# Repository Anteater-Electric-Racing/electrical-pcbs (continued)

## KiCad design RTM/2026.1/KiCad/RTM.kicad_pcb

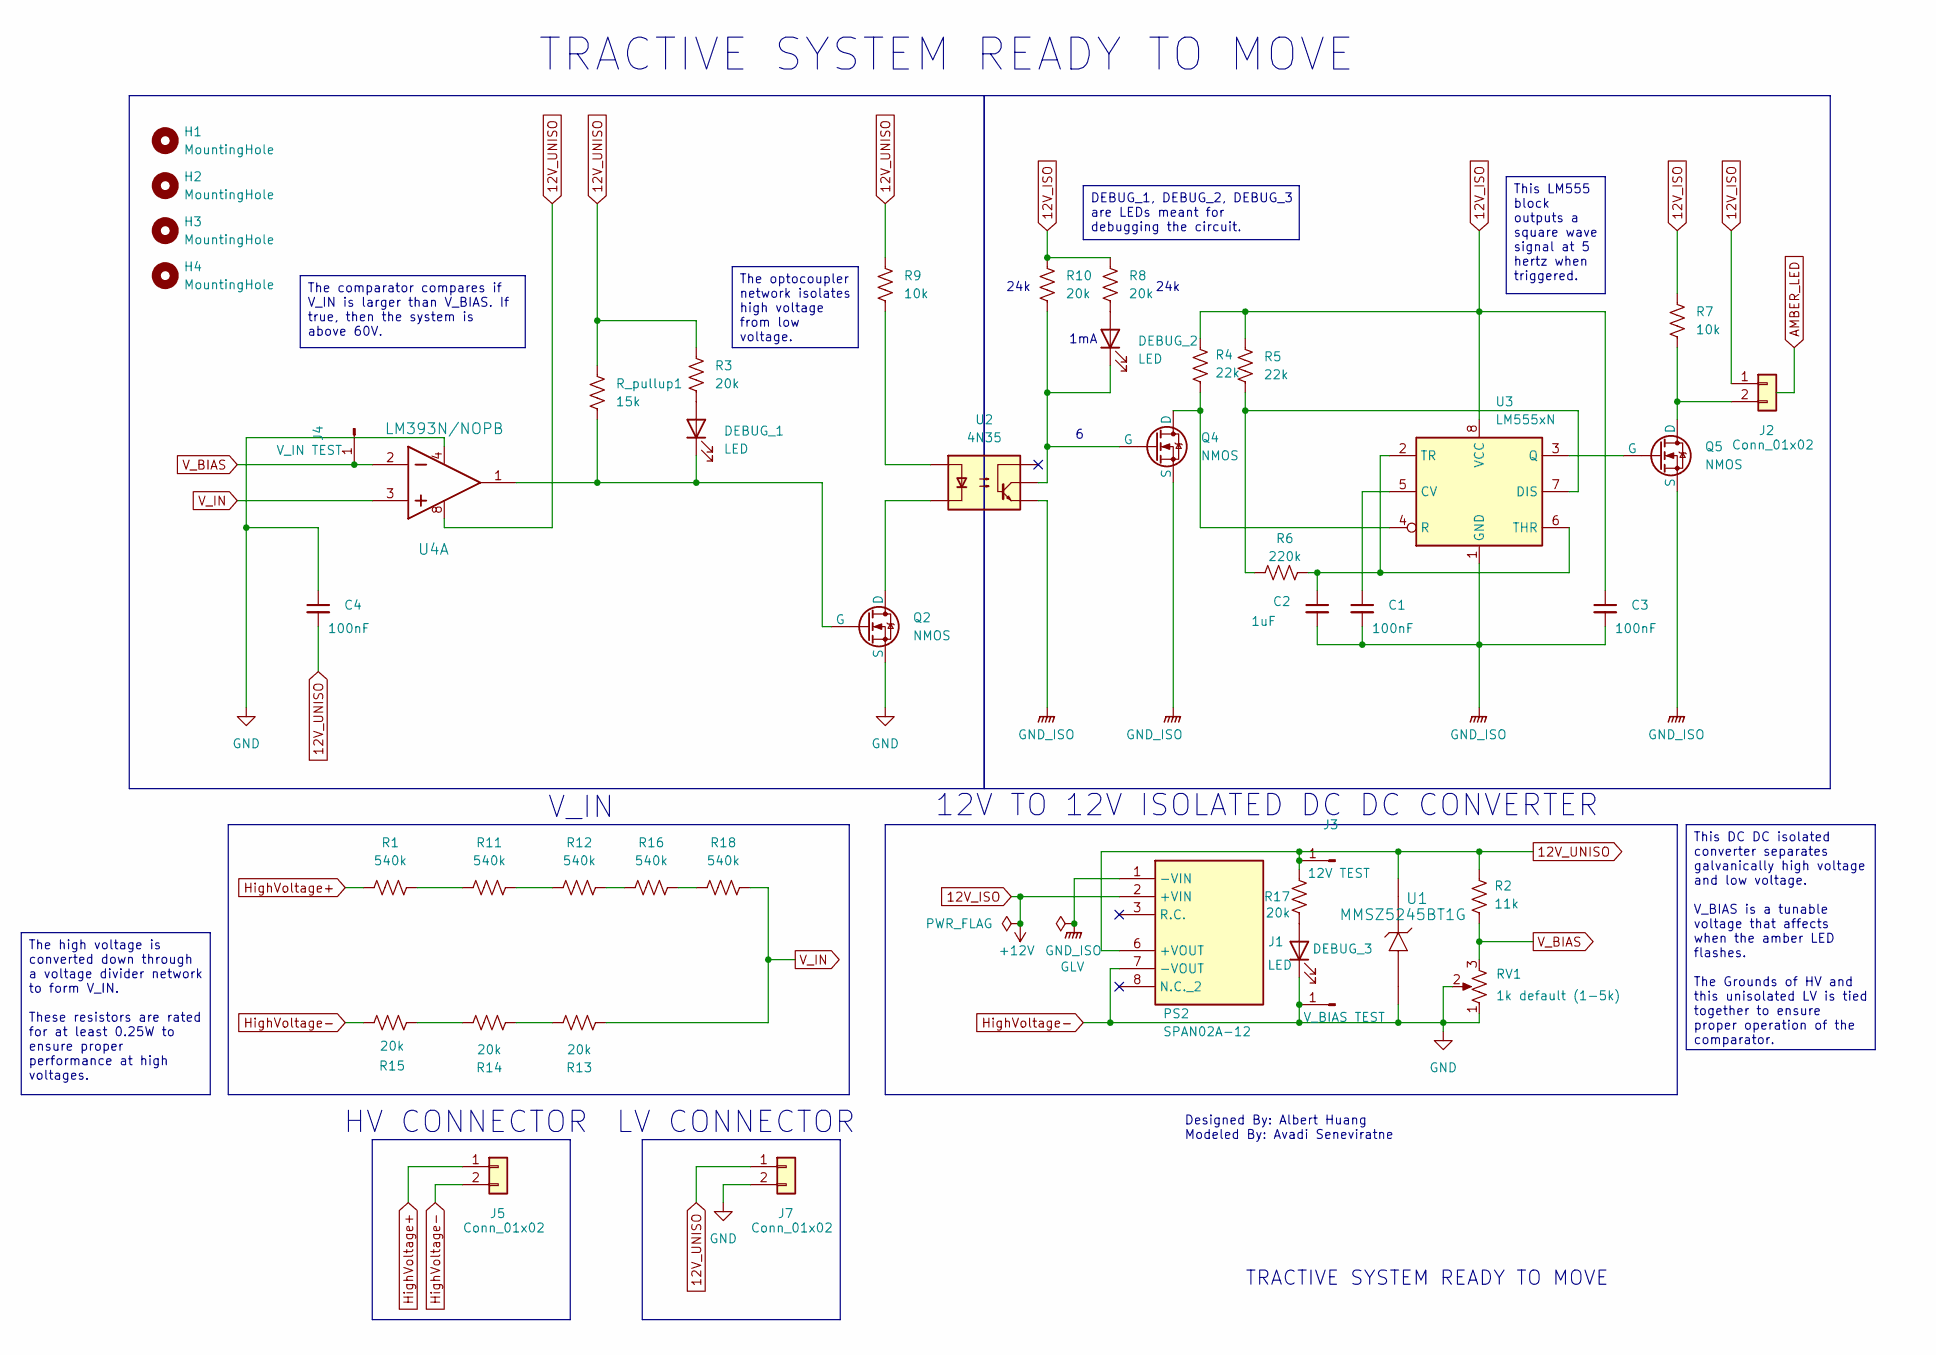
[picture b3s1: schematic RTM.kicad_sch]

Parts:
C1, C3, C4: 100nF; C_0805_2012Metric
C2: 1uF; C_0805_2012Metric
DEBUG_1, DEBUG_2, DEBUG_3: LED; LED_D5.0mm
H1, H2, H3, H4: MountingHole; MountingHole_3.2mm_M3
J1: V_BIAS TEST; TestPoint_Loop_D3.80mm_Drill2.0mm
J2, J5, J7: Conn_01x02; Molex_Mini-Fit_Jr_5566-02A2_2x01_P4.20mm_Vertical
J3: 12V TEST; TestPoint_Loop_D3.80mm_Drill2.0mm
J4: V_IN TEST; TestPoint_Loop_D3.80mm_Drill2.0mm
PS2: SPAN02A-12; SPAN02A12; Mouser Part Number 709-SPAN02A-12
Q2, Q4, Q5: NMOS; TO-220-3_Vertical
R1, R11, R12, R16, R18: 540k; R_0805_2012Metric
R2: 11k; R_0805_2012Metric
R3, R8, R10, R13, R14, R15, R17: 20k; R_0805_2012Metric
R4, R5: 22k; R_0805_2012Metric
R6: 220k; R_0805_2012Metric
R7, R9: 10k; R_0805_2012Metric
RV1: 1k default (1-5k); Potentiometer_Bourns_3296Y_Vertical
R_pullup1: 15k; R_0805_2012Metric
U1: MMSZ5245BT1G; D_SOD-123
U2: 4N35; DIP-6_W7.62mm
U3: LM555xN; DIP-8_W7.62mm
U4: LM393N/NOPB; DIP-8_W7.62mm

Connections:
12V_ISO: C3.1, J2.1, PS2.2 (+VIN), R4.1, R5.1, R7.1, R8.1, R10.1, U3.8 (VCC)
12V_UNISO: C4.2, J3.1, J7.1, PS2.6 (+VOUT), R2.1, R3.1, R9.1, R17.1, R_pullup1.1, U1.1 (CATHODE), U4.8 (V+)
GND_ISO: C1.2, C2.2, C3.2, PS2.1 (-VIN), Q4.3 (S), Q5.3 (S), U2.4, U3.1 (GND)
HighVoltage+: J5.1, R1.1
HighVoltage-: C4.1, DEBUG_3.1 (K), J1.1, J5.2, J7.2, PS2.7 (-VOUT), Q2.3 (S), R15.2, RV1.1, RV1.2, U1.2 (ANODE), U4.4 (GND)
unnamed: DEBUG_1.2 (A), R3.2
unnamed: DEBUG_1.1 (K), Q2.2 (G), R_pullup1.2, U4.1 (OUT)
unnamed: DEBUG_2.2 (A), R8.2
unnamed: DEBUG_2.1 (K), Q4.2 (G), R10.2, U2.5
unnamed: DEBUG_3.2 (A), R17.2
unnamed: J2.2, Q5.1 (D), R7.2
unnamed: Q2.1 (D), U2.2
unnamed: Q4.1 (D), R4.2, U3.4 (R)
unnamed: Q5.2 (G), U3.3 (Q)
unnamed: R1.2, R11.2
unnamed: R9.2, U2.1
unnamed: R11.1, R12.1
unnamed: R12.2, R16.1
unnamed: R13.2, R14.2
unnamed: R14.1, R15.1
unnamed: R16.2, R18.1
unnamed: C1.1, U3.5 (CV)
unnamed: R5.2, R6.1, U3.7 (DIS)
unnamed: C2.1, R6.2, U3.2 (TR), U3.6 (THR)
V_BIAS: J4.1, R2.2, RV1.3, U4.2 (IN-)
V_IN: R13.1, R18.2, U4.3 (IN+)

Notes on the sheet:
12V TO 12V ISOLATED DC DC CONVERTER
V_IN
TRACTIVE SYSTEM READY TO MOVE
24k
1mA
24k
LV CONNECTOR
TRACTIVE SYSTEM READY TO MOVE
Designed By: Albert Huang Modeled By: Avadi Seneviratne
HV CONNECTOR
This DC DC isolated converter separates galvanically high voltage and low voltage. V_BIAS is a tunable voltage that affects when the amber LED flashes. The Grounds of HV and this unisolated LV is tied together to ensure proper operation of the comparator.
The comparator compares if V_IN is larger than V_BIAS. If true, then the system is above 60V.
The high voltage is converted down through a voltage divider network to form V_IN. These resistors are rated for at least 0.25W to ensure proper performance at high voltages.
This LM555 block outputs a square wave signal at 5 hertz when triggered.
DEBUG_1, DEBUG_2, DEBUG_3 are LEDs meant for debugging the circuit.
The optocoupler network isolates high voltage from low voltage.

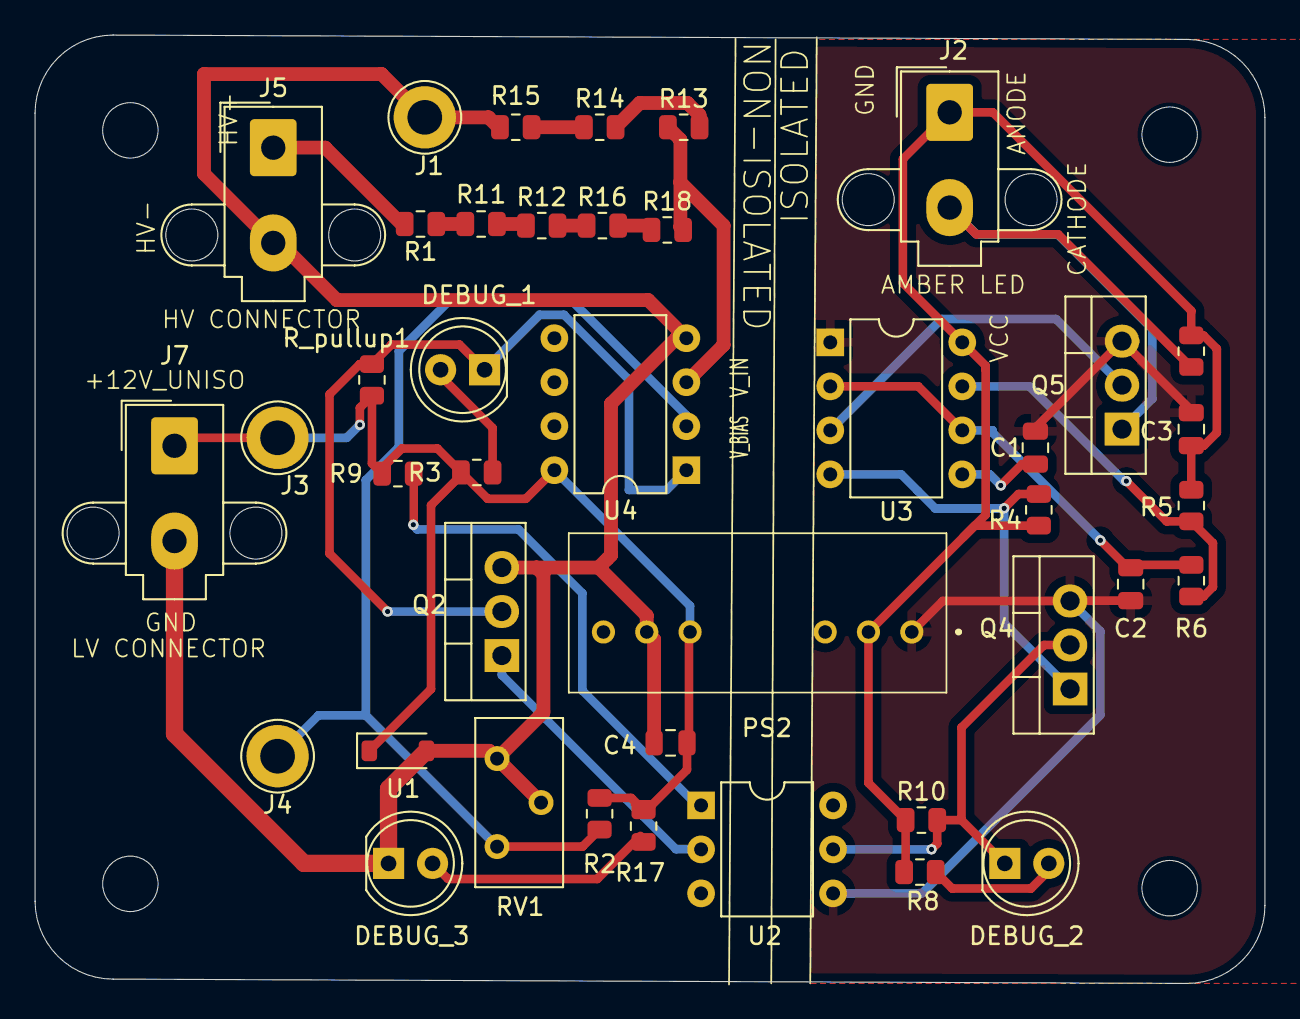
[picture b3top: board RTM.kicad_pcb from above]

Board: 2 copper layers, 71.0 x 54.8 mm, 45 parts (0 on the bottom side), 26 nets.

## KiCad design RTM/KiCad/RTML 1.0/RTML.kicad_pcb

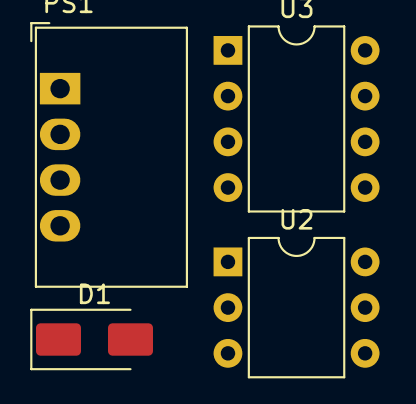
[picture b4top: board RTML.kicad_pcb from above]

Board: 2 copper layers, 4 parts (0 on the bottom side), 4 nets, no tracks yet.

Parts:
D1: US2AA; D_SMA
PS1: MEE3S1212SC; Converter_DCDC_Murata_MEE3SxxxxSC_THT
U2: 4N35; DIP-6_W7.62mm
U3: LM555xN; DIP-8_W7.62mm

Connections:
12V_UNISO: D1.1 (K), PS1.4 (+Vout)
GND: D1.2 (A), PS1.3 (-Vout)
GND_ISO: PS1.1 (-Vin), U2.4, U3.1 (GND)
unnamed: U3.2 (TR), U3.6 (THR)
